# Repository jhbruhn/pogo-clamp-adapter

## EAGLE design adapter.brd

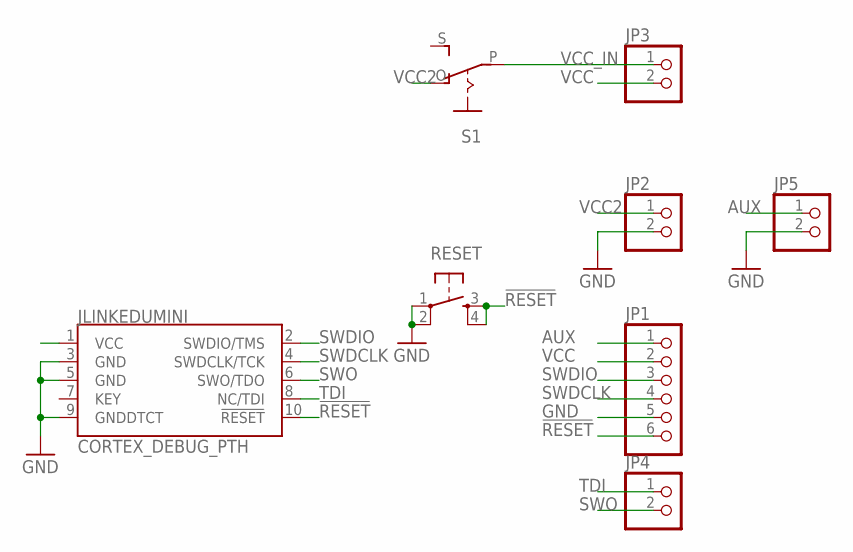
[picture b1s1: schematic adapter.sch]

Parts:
JLINKEDUMINI: CORTEX_DEBUG_PTH; 2X5-PTH-1.27MM
JP1: PINHD-1X6; 1X06
JP2, JP3, JP4, JP5: PINHD-1X2; 1X02
RESET: TAC_SWITCHPTH; TACTILE-PTH
S1: S-ON-ON; ES_100SP1T6B11M2QEH

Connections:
!RESET: JLINKEDUMINI.10 (!RESET), JP1.6, RESET.3, RESET.4
AUX: JP1.1, JP5.1
GND: JLINKEDUMINI.3 (GND), JLINKEDUMINI.5 (GND), JLINKEDUMINI.9 (GNDDTCT), JP1.5, JP2.2, JP5.2, RESET.1, RESET.2
SWDCLK: JLINKEDUMINI.4 (SWDCLK/TCK), JP1.4
SWDIO: JLINKEDUMINI.2 (SWDIO/TMS), JP1.3
SWO: JLINKEDUMINI.6 (SWO/TDO), JP4.2
TDI: JLINKEDUMINI.8 (NC/TDI), JP4.1
VCC: JLINKEDUMINI.1 (VCC), JP1.2, JP3.2
VCC2: JP2.1, S1.O
VCC_IN: JP3.1, S1.P

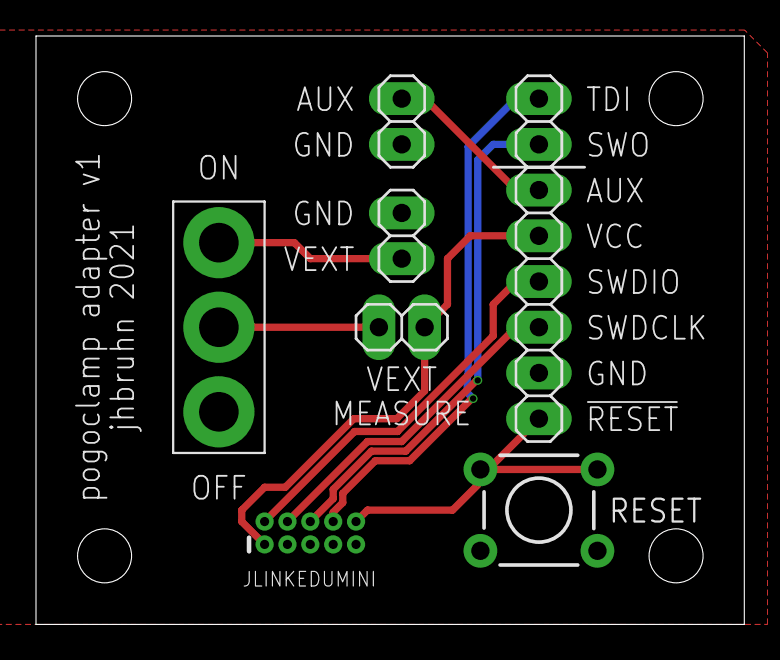
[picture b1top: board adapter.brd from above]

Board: 2 copper layers, 39.4 x 32.7 mm, 9 parts (1 on the bottom side), 10 nets.

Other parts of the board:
U$1: FERN_PATTERN_MULTI
